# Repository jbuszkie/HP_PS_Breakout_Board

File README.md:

# HP_PS_Breakout_Board
Breakout board for an HP server power supply.

HP_power_supply_breakout.zip -> Archived kicad design

HP_power_supply_breakout_art_V1.0.zip -> Zipped up artwork files sent to jlcpcb

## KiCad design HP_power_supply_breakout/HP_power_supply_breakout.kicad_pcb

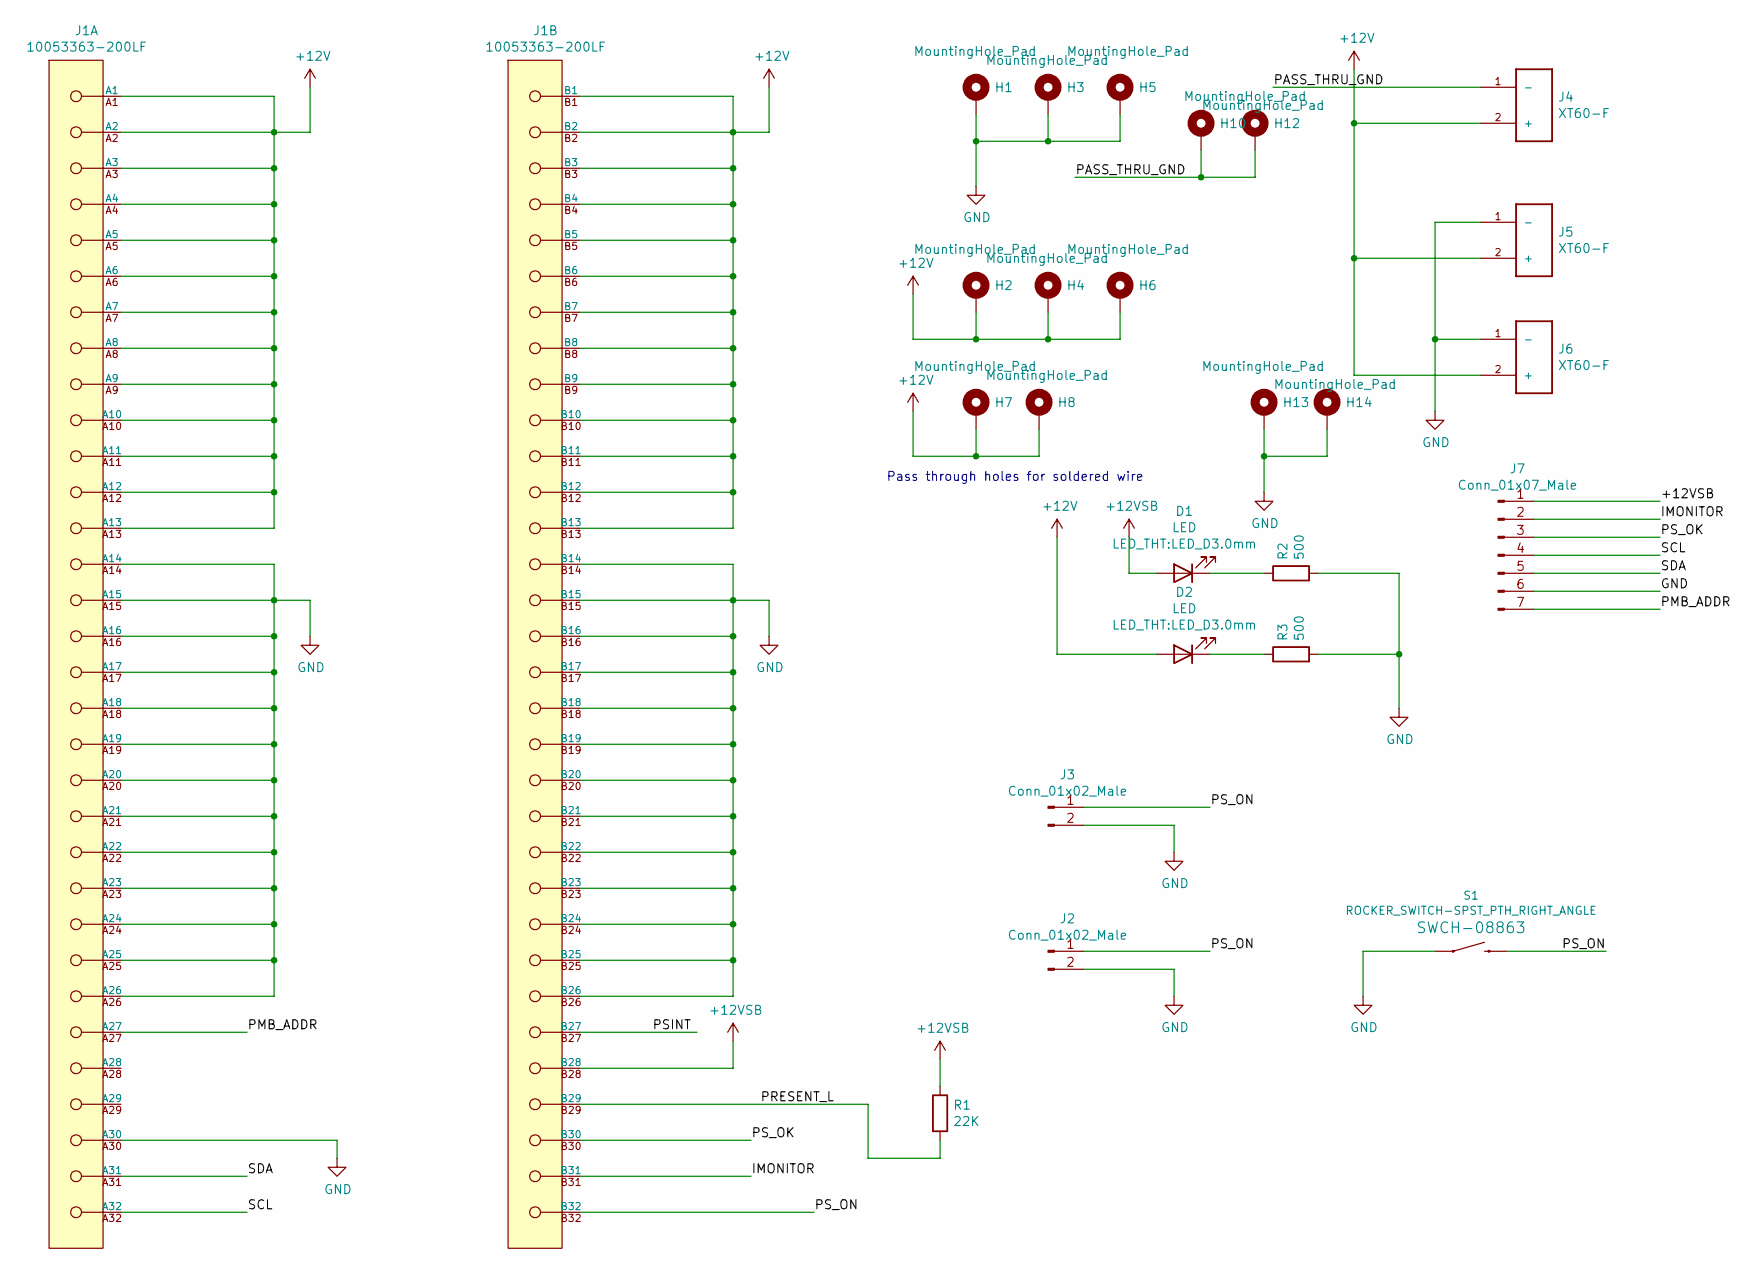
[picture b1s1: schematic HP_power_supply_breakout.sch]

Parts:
D1, D2: LED; LED_D3.0mm
H1, H2, H3, H4, H5, H6: MountingHole_Pad; MountingHole_5.5mm_Pad_Via
H7, H8, H10, H12, H13, H14: MountingHole_Pad; MountingHole_3.2mm_M3_Pad_Via
J1: 10053363-200LF; Amphenol_ICC-10053363-200LF-0-0-MFG; current rating 7A; mouser part number 649-10053363-200LF; digikey description CONN EDGE DUAL FMALE 64POS 0.100
J2, J3: Conn_01x02_Male; PinHeader_1x02_P2.54mm_Vertical
J4, J5, J6: XT60-F; AMASS_XT60-F_1x02_P7.20mm_Vertical
J7: Conn_01x07_Male; PinHeader_1x07_P2.54mm_Vertical
R1: 22K; R_0402_1005Metric
R2, R3: 500; R_0402_1005Metric
S1: ROCKER_SWITCH-SPST_PTH_RIGHT_ANGLE; RockerSwitch_RA_R1966A

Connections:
+12V: D2.2 (A), H2.1, H4.1, H6.1, H7.1, H8.1, J1.A1, J1.A2, J1.A3, J1.A4, J1.A5, J1.A6, J1.A7, J1.A8, J1.A9, J1.A10, J1.A11, J1.A12, J1.A13, J1.B1, J1.B2, J1.B3, J1.B4, J1.B5, J1.B6, J1.B7, J1.B8, J1.B9, J1.B10, J1.B11, J1.B12, J1.B13, J4.2 (+), J5.2 (+), J6.2 (+)
+12VSB: D1.2 (A), J1.B28, J7.1, R1.1
/IMONITOR: J1.B31, J7.2
/PASS_THRU_GND: H10.1, H12.1, J4.1 (-)
/PMB_ADDR: J1.A27, J7.7
/PRESENT_L: J1.B29, R1.2
/PSINT: J1.B27
/PS_OK: J1.B30, J7.3
/PS_ON: J1.B32, J2.1, J3.1, S1.2
/SCL: J1.A32, J7.4
/SDA: J1.A31, J7.5
GND: H1.1, H3.1, H5.1, H13.1, H14.1, J1.A14, J1.A15, J1.A16, J1.A17, J1.A18, J1.A19, J1.A20, J1.A21, J1.A22, J1.A23, J1.A24, J1.A25, J1.A26, J1.A30, J1.B14, J1.B15, J1.B16, J1.B17, J1.B18, J1.B19, J1.B20, J1.B21, J1.B22, J1.B23, J1.B24, J1.B25, J1.B26, J2.2, J3.2, J5.1 (-), J6.1 (-), J7.6, R2.2, R3.2, S1.1
unnamed: D1.1 (K), R2.1
unnamed: D2.1 (K), R3.1

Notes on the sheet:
Pass through holes for soldered wire

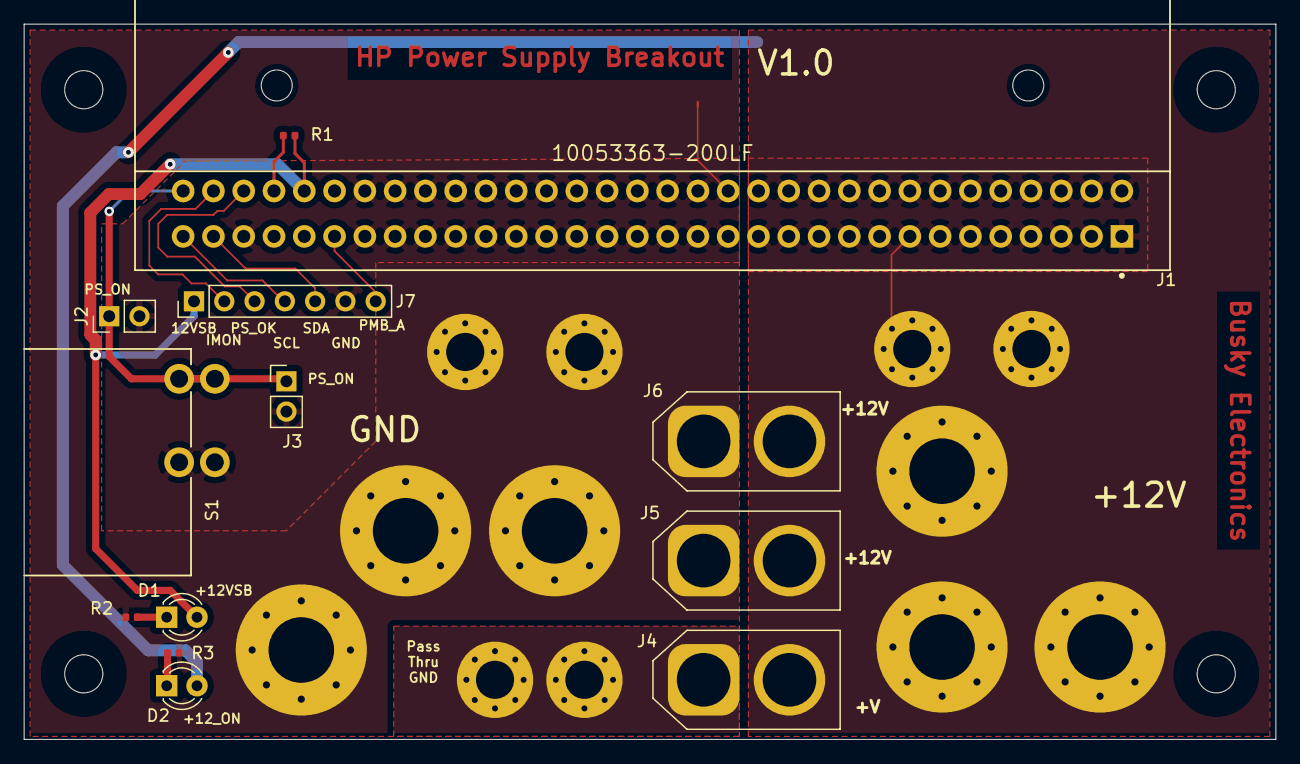
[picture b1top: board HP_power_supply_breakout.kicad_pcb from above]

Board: 2 copper layers, 105.0 x 60.0 mm, 25 parts (0 on the bottom side), 13 nets.

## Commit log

2020-10-20 Add all the kicad files individually....
